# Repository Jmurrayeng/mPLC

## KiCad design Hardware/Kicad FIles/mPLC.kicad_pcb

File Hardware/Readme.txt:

Minimally viable PLC like device based on an RP2040

The board requires a 24VDC power supply and produces a 10V and 5V power supply on the power out connectors
The internal 3.3VDC power supply supply is accessable via the programming/expansion header

There are 11 24VDC inputs (gpio 0 to 10) and 11 open collector outputs (gpio 11-22)
The 4 ADC (gpio 26 to 29) are suitable for 0-10V

The remaining 4 gpio are taken to the programming/expansion header along with serial wire debug

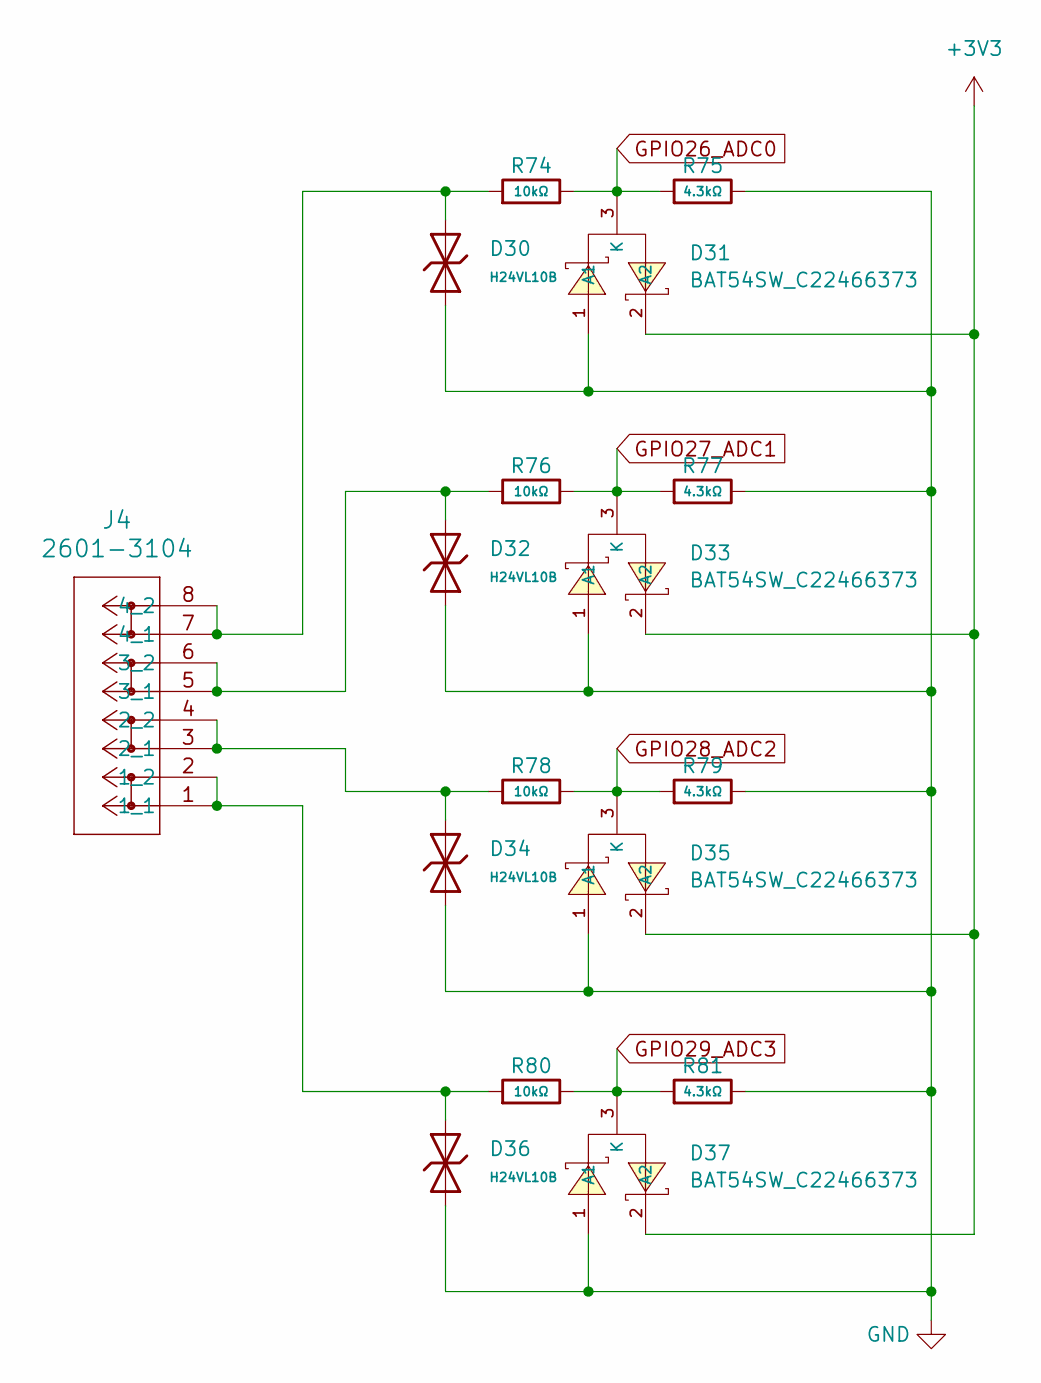
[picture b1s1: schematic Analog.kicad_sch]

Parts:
D30, D32, D34, D36: H24VL10B; D_DFN1006-2L; Part H24VL10B; LCSC C20617912
D31, D33, D35, D37: BAT54SW_C22466373; SOT-323-3_L2.0-W1.3-P1.30-LS2.1-BR-2; Part BAT54SW; LCSC C22466373
J4: 2601-3104; CONN4_2601-3104_WAG
R74, R76, R78, R80: 10kΩ; R_0805; Overload Voltage (Max) 150V; Tolerance ±1%; Part 0805W8F1002T5E; LCSC C17414
R75, R77, R79, R81: 4.3kΩ; R_0805; Overload Voltage (Max) 150V; Tolerance ±1%; Part 0805W8F4301T5E; LCSC C17667

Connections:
+3V3: D31.2 (A2), D33.2 (A2), D35.2 (A2), D37.2 (A2); also elsewhere on the board
GND: D30.1, D31.1 (A1), D32.1, D33.1 (A1), D34.1, D35.1 (A1), D36.1, D37.1 (A1), R75.2, R77.2, R79.2, R81.2; also elsewhere on the board
GPIO26_ADC0: D31.3 (K), R74.2, R75.1; also elsewhere on the board
GPIO27_ADC1: D33.3 (K), R76.2, R77.1; also elsewhere on the board
GPIO28_ADC2: D35.3 (K), R78.2, R79.1; also elsewhere on the board
GPIO29_ADC3: D37.3 (K), R80.2, R81.1; also elsewhere on the board
unnamed: D36.2, J4.1 (1_1), J4.2 (1_2), R80.1
unnamed: D34.2, J4.3 (2_1), J4.4 (2_2), R78.1
unnamed: D32.2, J4.5 (3_1), J4.6 (3_2), R76.1
unnamed: D30.2, J4.7 (4_1), J4.8 (4_2), R74.1

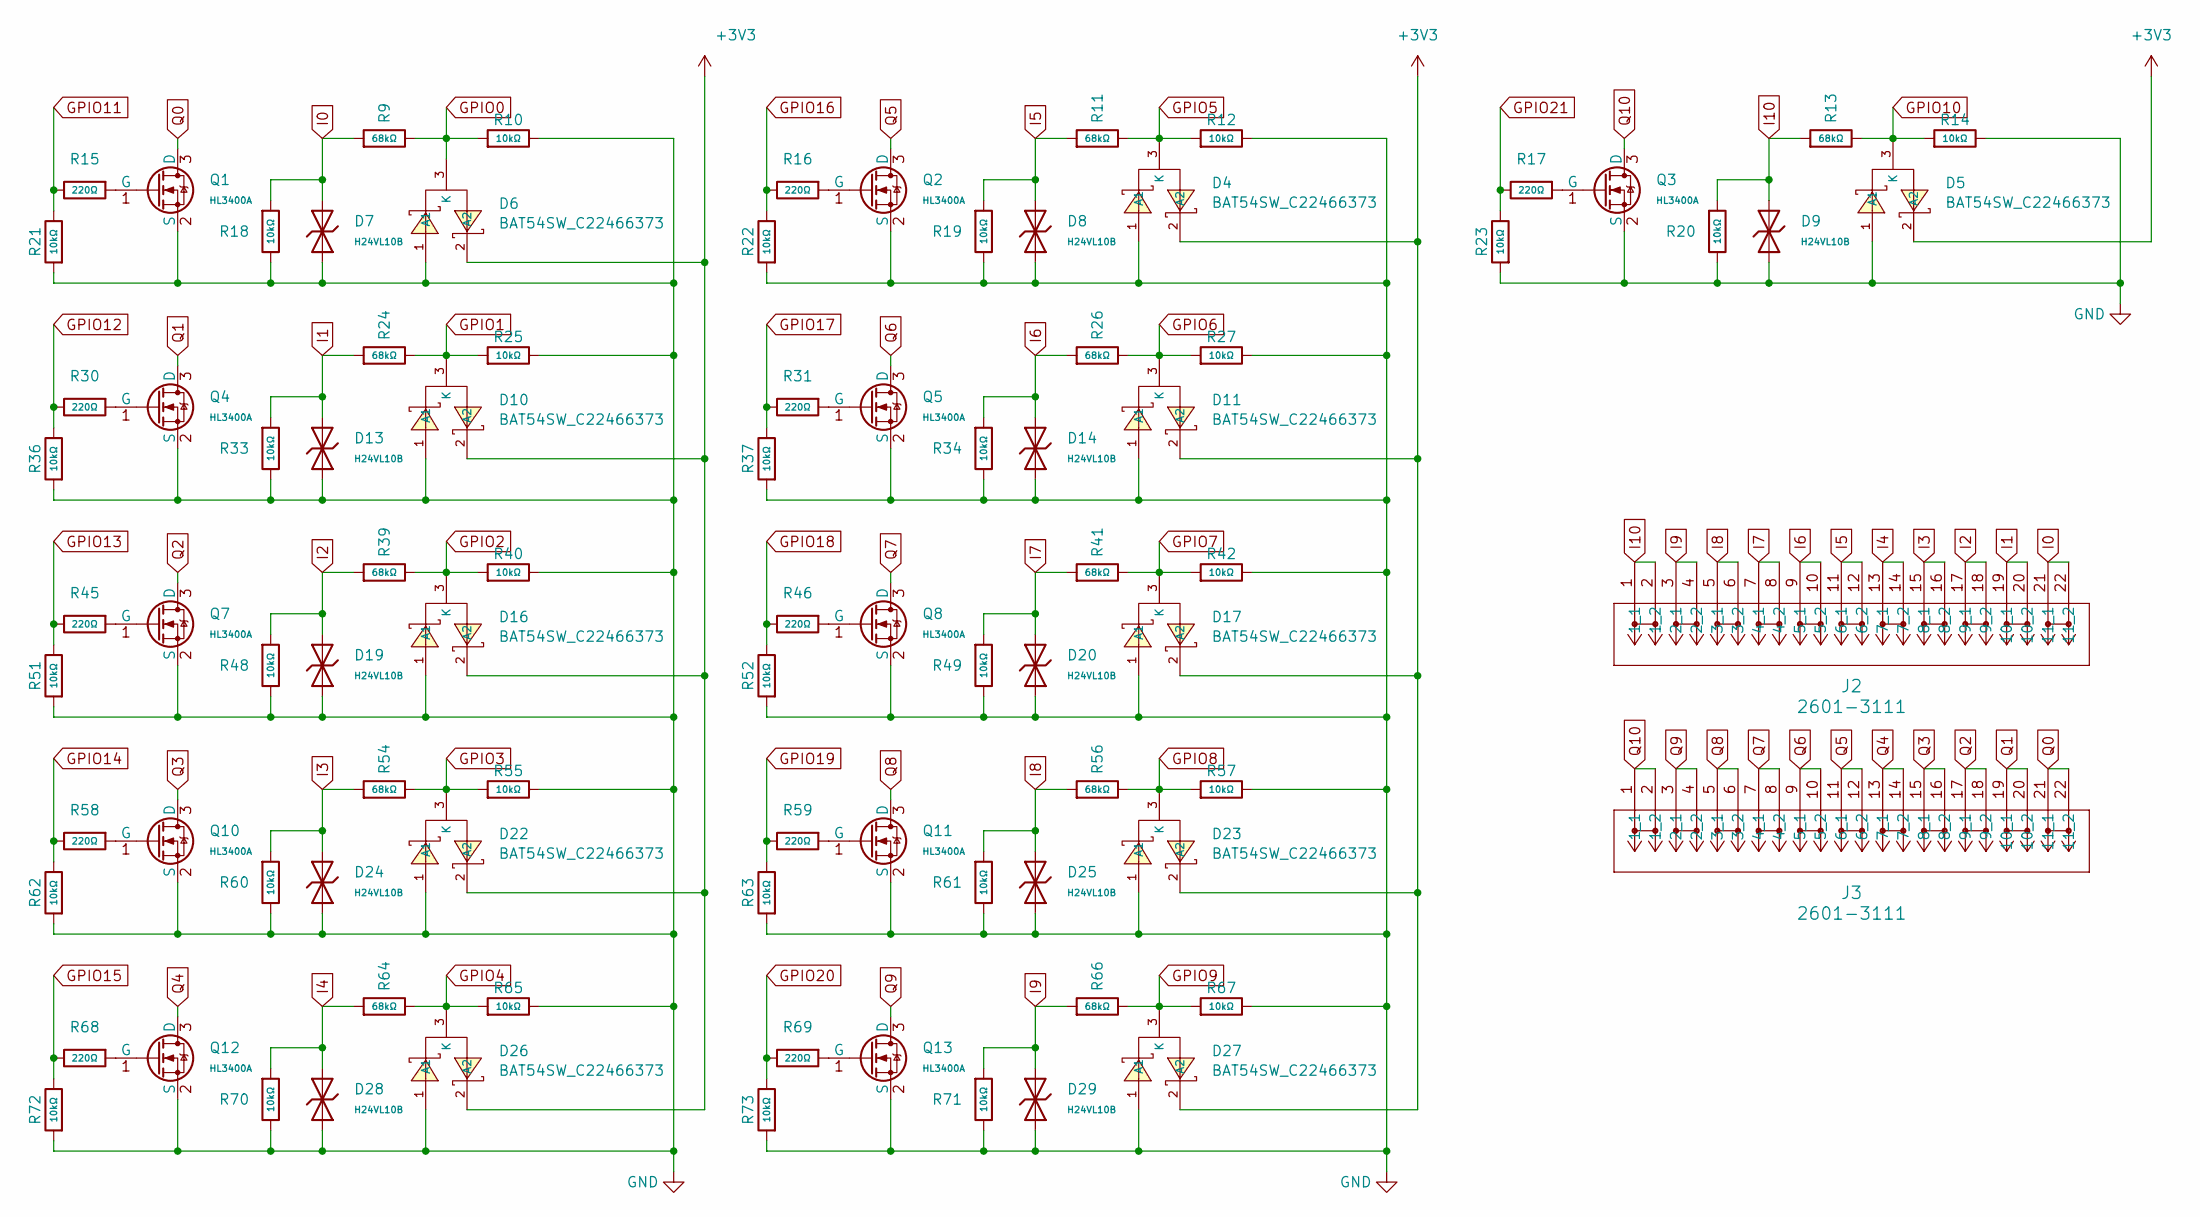
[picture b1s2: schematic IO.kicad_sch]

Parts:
D4, D5, D6, D10, D11, D16, D17, D22, D23, D26, D27: BAT54SW_C22466373; SOT-323-3_L2.0-W1.3-P1.30-LS2.1-BR-2; Part BAT54SW; LCSC C22466373
D7, D8, D9, D13, D14, D19, D20, D24, D25, D28, D29: H24VL10B; D_DFN1006-2L; Part H24VL10B; LCSC C20617912
J2, J3: 2601-3111; CONN11_2601-3111_WAG
Q1, Q2, Q3, Q4, Q5, Q7, Q8, Q10, Q11, Q12, Q13: HL3400A; Q_SOT-23; Part HL3400A; LCSC C7420348
R9, R11, R13, R24, R26, R39, R41, R54, R56, R64, R66: 68kΩ; R_0805; Overload Voltage (Max) 150V; Tolerance ±1%; Part 0805W8F6802T5E; LCSC C17801
R10, R12, R14, R21, R22, R23, R25, R27, R36, R37, R40, R42, R51, R52, R55, R57, R62, R63, R65, R67, R72, R73: 10kΩ; R_0805; Overload Voltage (Max) 150V; Tolerance ±1%; Part 0805W8F1002T5E; LCSC C17414
R15, R16, R17, R30, R31, R45, R46, R58, R59, R68, R69: 220Ω; R_0805; Overload Voltage (Max) 150V; Tolerance ±1%; Part 0805W8F2200T5E; LCSC C17557
R18, R19, R20, R33, R34, R48, R49, R60, R61, R70, R71: 10kΩ; R_1206; Overload Voltage (Max) 200V; Tolerance ±1%; Part 1206W4F1002T5E; LCSC C17902

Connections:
+3V3: D4.2 (A2), D5.2 (A2), D6.2 (A2), D10.2 (A2), D11.2 (A2), D16.2 (A2), D17.2 (A2), D22.2 (A2), D23.2 (A2), D26.2 (A2), D27.2 (A2); also elsewhere on the board
GND: D4.1 (A1), D5.1 (A1), D6.1 (A1), D7.1, D8.1, D9.1, D10.1 (A1), D11.1 (A1), D13.1, D14.1, D16.1 (A1), D17.1 (A1), D19.1, D20.1, D22.1 (A1), D23.1 (A1), D24.1, D25.1, D26.1 (A1), D27.1 (A1), D28.1, D29.1, Q1.2 (S), Q2.2 (S), Q3.2 (S), Q4.2 (S), Q5.2 (S), Q7.2 (S), Q8.2 (S), Q10.2 (S), Q11.2 (S), Q12.2 (S), Q13.2 (S), R10.2, R12.2, R14.2, R18.2, R19.2, R20.2, R21.1, R22.1, R23.1, R25.2, R27.2, R33.2, R34.2, R36.1, R37.1, R40.2, R42.2, R48.2, R49.2, R51.1, R52.1, R55.2, R57.2, R60.2, R61.2, R62.1, R63.1, R65.2, R67.2, R70.2, R71.2, R72.1, R73.1; also elsewhere on the board
GPIO0: D6.3 (K), R9.2, R10.1; also elsewhere on the board
GPIO1: D10.3 (K), R24.2, R25.1; also elsewhere on the board
GPIO2: D16.3 (K), R39.2, R40.1; also elsewhere on the board
GPIO3: D22.3 (K), R54.2, R55.1; also elsewhere on the board
GPIO4: D26.3 (K), R64.2, R65.1; also elsewhere on the board
GPIO5: D4.3 (K), R11.2, R12.1; also elsewhere on the board
GPIO6: D11.3 (K), R26.2, R27.1; also elsewhere on the board
GPIO7: D17.3 (K), R41.2, R42.1; also elsewhere on the board
GPIO8: D23.3 (K), R56.2, R57.1; also elsewhere on the board
GPIO9: D27.3 (K), R66.2, R67.1; also elsewhere on the board
GPIO10: D5.3 (K), R13.2, R14.1; also elsewhere on the board
GPIO11: R15.2, R21.2; also elsewhere on the board
GPIO12: R30.2, R36.2; also elsewhere on the board
GPIO13: R45.2, R51.2; also elsewhere on the board
GPIO14: R58.2, R62.2; also elsewhere on the board
GPIO15: R68.2, R72.2; also elsewhere on the board
GPIO16: R16.2, R22.2; also elsewhere on the board
GPIO17: R31.2, R37.2; also elsewhere on the board
GPIO18: R46.2, R52.2; also elsewhere on the board
GPIO19: R59.2, R63.2; also elsewhere on the board
GPIO20: R69.2, R73.2; also elsewhere on the board
GPIO21: R17.2, R23.2; also elsewhere on the board
I0: D7.2, J2.21 (11_1), J2.22 (11_2), R9.1, R18.1
I1: D13.2, J2.19 (10_1), J2.20 (10_2), R24.1, R33.1
I2: D19.2, J2.17 (9_1), J2.18 (9_2), R39.1, R48.1
I3: D24.2, J2.15 (8_1), J2.16 (8_2), R54.1, R60.1
I4: D28.2, J2.13 (7_1), J2.14 (7_2), R64.1, R70.1
I5: D8.2, J2.11 (6_1), J2.12 (6_2), R11.1, R19.1
I6: D14.2, J2.9 (5_1), J2.10 (5_2), R26.1, R34.1
I7: D20.2, J2.7 (4_1), J2.8 (4_2), R41.1, R49.1
I8: D25.2, J2.5 (3_1), J2.6 (3_2), R56.1, R61.1
I9: D29.2, J2.3 (2_1), J2.4 (2_2), R66.1, R71.1
I10: D9.2, J2.1 (1_1), J2.2 (1_2), R13.1, R20.1
unnamed: Q1.1 (G), R15.1
unnamed: Q2.1 (G), R16.1
unnamed: Q3.1 (G), R17.1
unnamed: Q4.1 (G), R30.1
unnamed: Q5.1 (G), R31.1
unnamed: Q7.1 (G), R45.1
unnamed: Q8.1 (G), R46.1
unnamed: Q10.1 (G), R58.1
unnamed: Q11.1 (G), R59.1
unnamed: Q12.1 (G), R68.1
unnamed: Q13.1 (G), R69.1
Q0: J3.21 (11_1), J3.22 (11_2), Q1.3 (D)
Q1: J3.19 (10_1), J3.20 (10_2), Q4.3 (D)
Q2: J3.17 (9_1), J3.18 (9_2), Q7.3 (D)
Q3: J3.15 (8_1), J3.16 (8_2), Q10.3 (D)
Q4: J3.13 (7_1), J3.14 (7_2), Q12.3 (D)
Q5: J3.11 (6_1), J3.12 (6_2), Q2.3 (D)
Q6: J3.9 (5_1), J3.10 (5_2), Q5.3 (D)
Q7: J3.7 (4_1), J3.8 (4_2), Q8.3 (D)
Q8: J3.5 (3_1), J3.6 (3_2), Q11.3 (D)
Q9: J3.3 (2_1), J3.4 (2_2), Q13.3 (D)
Q10: J3.1 (1_1), J3.2 (1_2), Q3.3 (D)

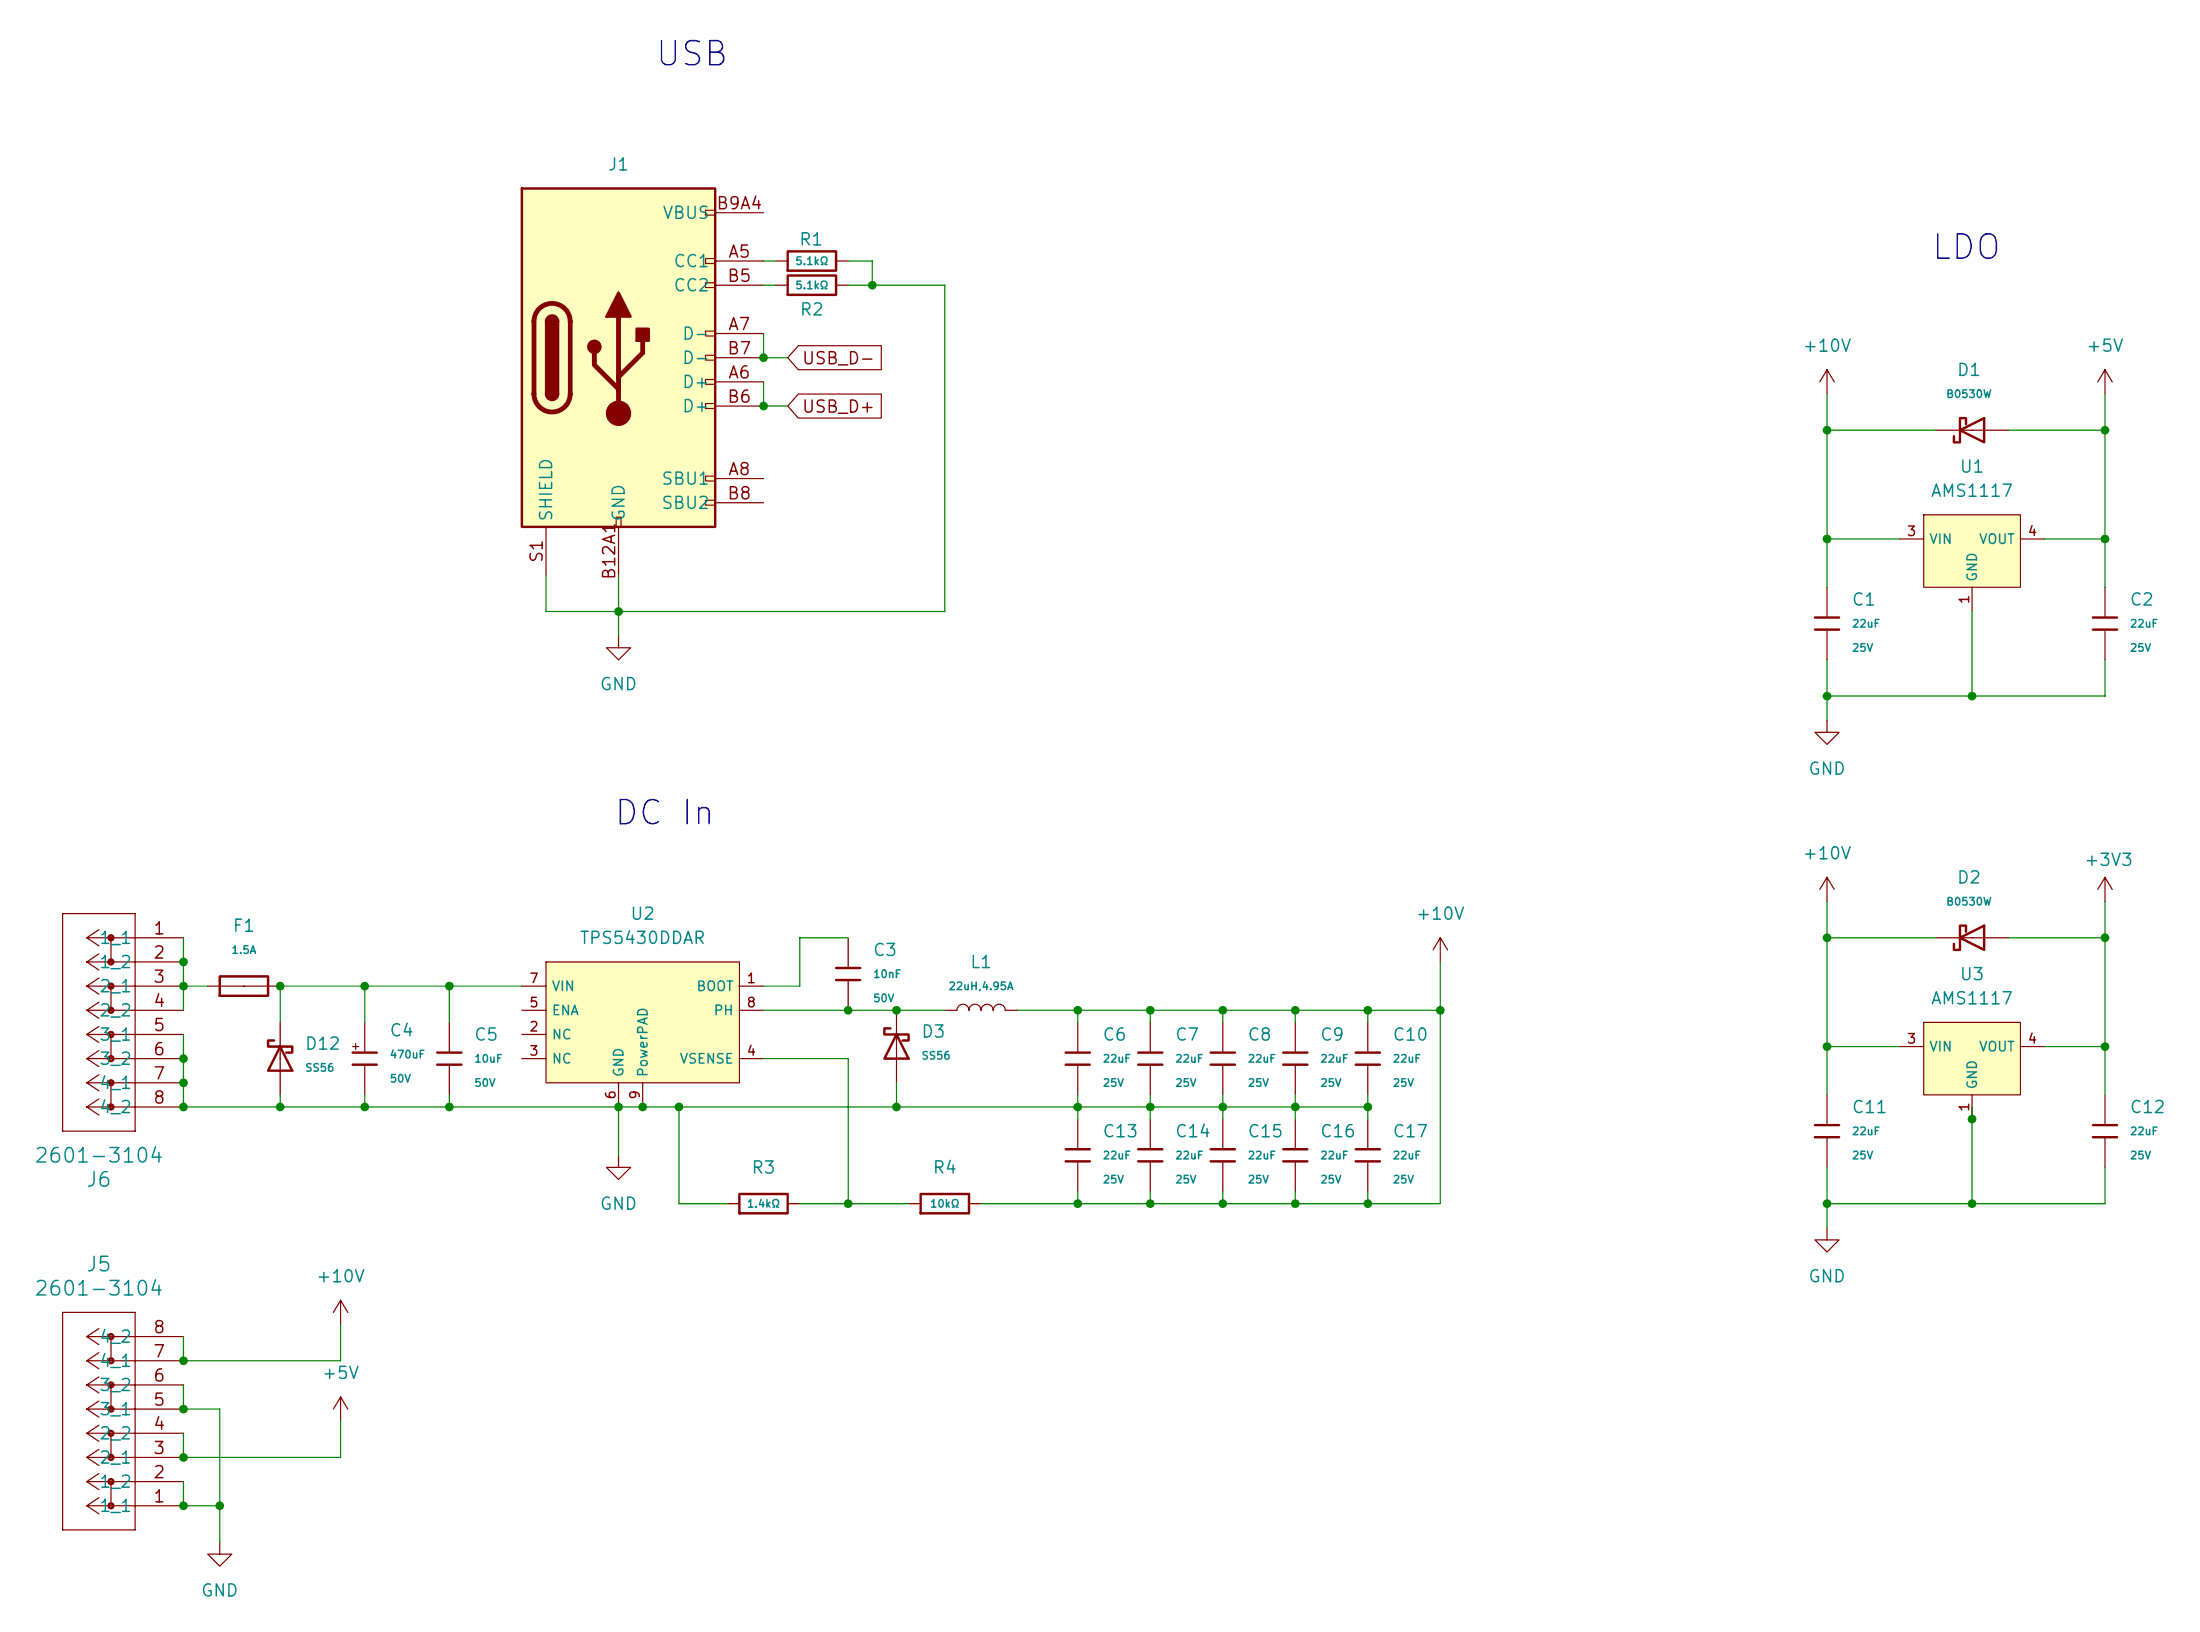
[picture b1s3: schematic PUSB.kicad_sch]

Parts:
C1, C2, C11, C12: 22uF; C_0805; Voltage Rated 25V; Tolerance ±20%; Part CL21A226MAQNNNE; LCSC C45783
C3: 10nF; C_0805; Voltage Rated 50V; Tolerance ±10%; Part CL21B103KBANNNC; LCSC C1710
C4: 470uF; C_Plugin,D10xL16mm; Voltage Rated 50V; Part EGT477M1HG16RRS0P; LCSC C3015599
C5: 10uF; C_0805; Voltage Rated 50V; Tolerance ±10%; Part GRM21BR61H106KE43L; LCSC C440198
C6, C7, C8, C9, C10, C13, C14, C15, C16, C17: 22uF; C_1206; Voltage Rated 25V; Tolerance ±10%; Part CL31A226KAHNNNE; LCSC C12891
D1, D2: B0530W; D_SOD-123; Part B0530W; LCSC C7502708
D3, D12: SS56; D_SMC; Part SS56; LCSC C2898934
F1: 1.5A; F_1206; Part SRF1206P150; LCSC C2838983
J1: Connector, USB-TYPE-C-16P; TYPE-C-SMD_HX-TYPE-C-16PIN; LCSC C2927039
J5, J6: 2601-3104; CONN4_2601-3104_WAG
L1: 22uH,4.95A; L_SMD,12.5x12.5mm; Part SMDRI129-220MT; LCSC C2924827
R1, R2: 5.1kΩ; R_0805; Overload Voltage (Max) 150V; Tolerance ±1%; Part 0805W8F5101T5E; LCSC C27834
R3: 1.4kΩ; R_0805; Part CR0805F81401G; LCSC C101470
R4: 10kΩ; R_0805; Overload Voltage (Max) 150V; Tolerance ±1%; Part 0805W8F1002T5E; LCSC C17414
U1: AMS1117; SOT-223_L6.5-W3.5-P2.30-LS7.0-BR; Output Voltage 5V~5V; Dropout Voltage 1.3V@(1A); Part AMS1117-5.0; LCSC C6187
U2: TPS5430DDAR; ESOP-8_L4.9-W3.9-P1.27-LS6.0-TL-EP; Output Voltage 1.221V~32.04V; Input Voltage 5.5V~36V; Part TPS5430DDAR; LCSC C9864
U3: AMS1117; SOT-223-3_L6.5-W3.4-P2.30-LS7.0-BR; Output Voltage 3.3V~3.3V; Dropout Voltage 1.3V@(800mA); Part AMS1117-3.3; LCSC C6186

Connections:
+3V3: C12.1, D2.2, U3.2 (VOUT), U3.4 (VOUT); also elsewhere on the board
+5V: C2.1, D1.2, J5.3 (2_1), J5.4 (2_2), U1.2 (VOUT), U1.4 (VOUT)
+10V: C1.1, C6.1, C7.1, C8.1, C9.1, C10.1, C11.1, C13.2, C14.2, C15.2, C16.2, C17.2, D1.1, D2.1, J5.7 (4_1), J5.8 (4_2), L1.2, R4.2, U1.3 (VIN), U3.3 (VIN)
GND: C1.2, C2.2, C4.2, C5.2, C6.2, C7.2, C8.2, C9.2, C10.2, C11.2, C12.2, C13.1, C14.1, C15.1, C16.1, C17.1, D3.2, D12.2, J1.A12B1 (GND), J1.B12A1 (GND), J1.S1 (SHIELD), J5.1 (1_1), J5.2 (1_2), J5.5 (3_1), J5.6 (3_2), J6.5 (3_1), J6.6 (3_2), J6.7 (4_1), J6.8 (4_2), R1.2, R2.2, R3.1, U1.1 (GND), U2.6 (GND), U2.9 (PowerPAD), U3.1 (GND); also elsewhere on the board
unnamed: J1.A5 (CC1), R1.1
unnamed: J1.B5 (CC2), R2.1
unnamed: J1.A9B4 (VBUS), J1.B9A4 (VBUS)
unnamed: F1.1, J6.1 (1_1), J6.2 (1_2), J6.3 (2_1), J6.4 (2_2)
unnamed: C3.1, U2.1 (BOOT)
unnamed: C3.2, D3.1, L1.1, U2.8 (PH)
unnamed: C4.1, C5.1, D12.1, F1.2, U2.7 (VIN)
unnamed: R3.2, R4.1, U2.4 (VSENSE)
USB_D+: J1.A6 (D+), J1.B6 (D+); also elsewhere on the board
USB_D-: J1.A7 (D-), J1.B7 (D-); also elsewhere on the board

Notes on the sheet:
LDO
USB
DC In

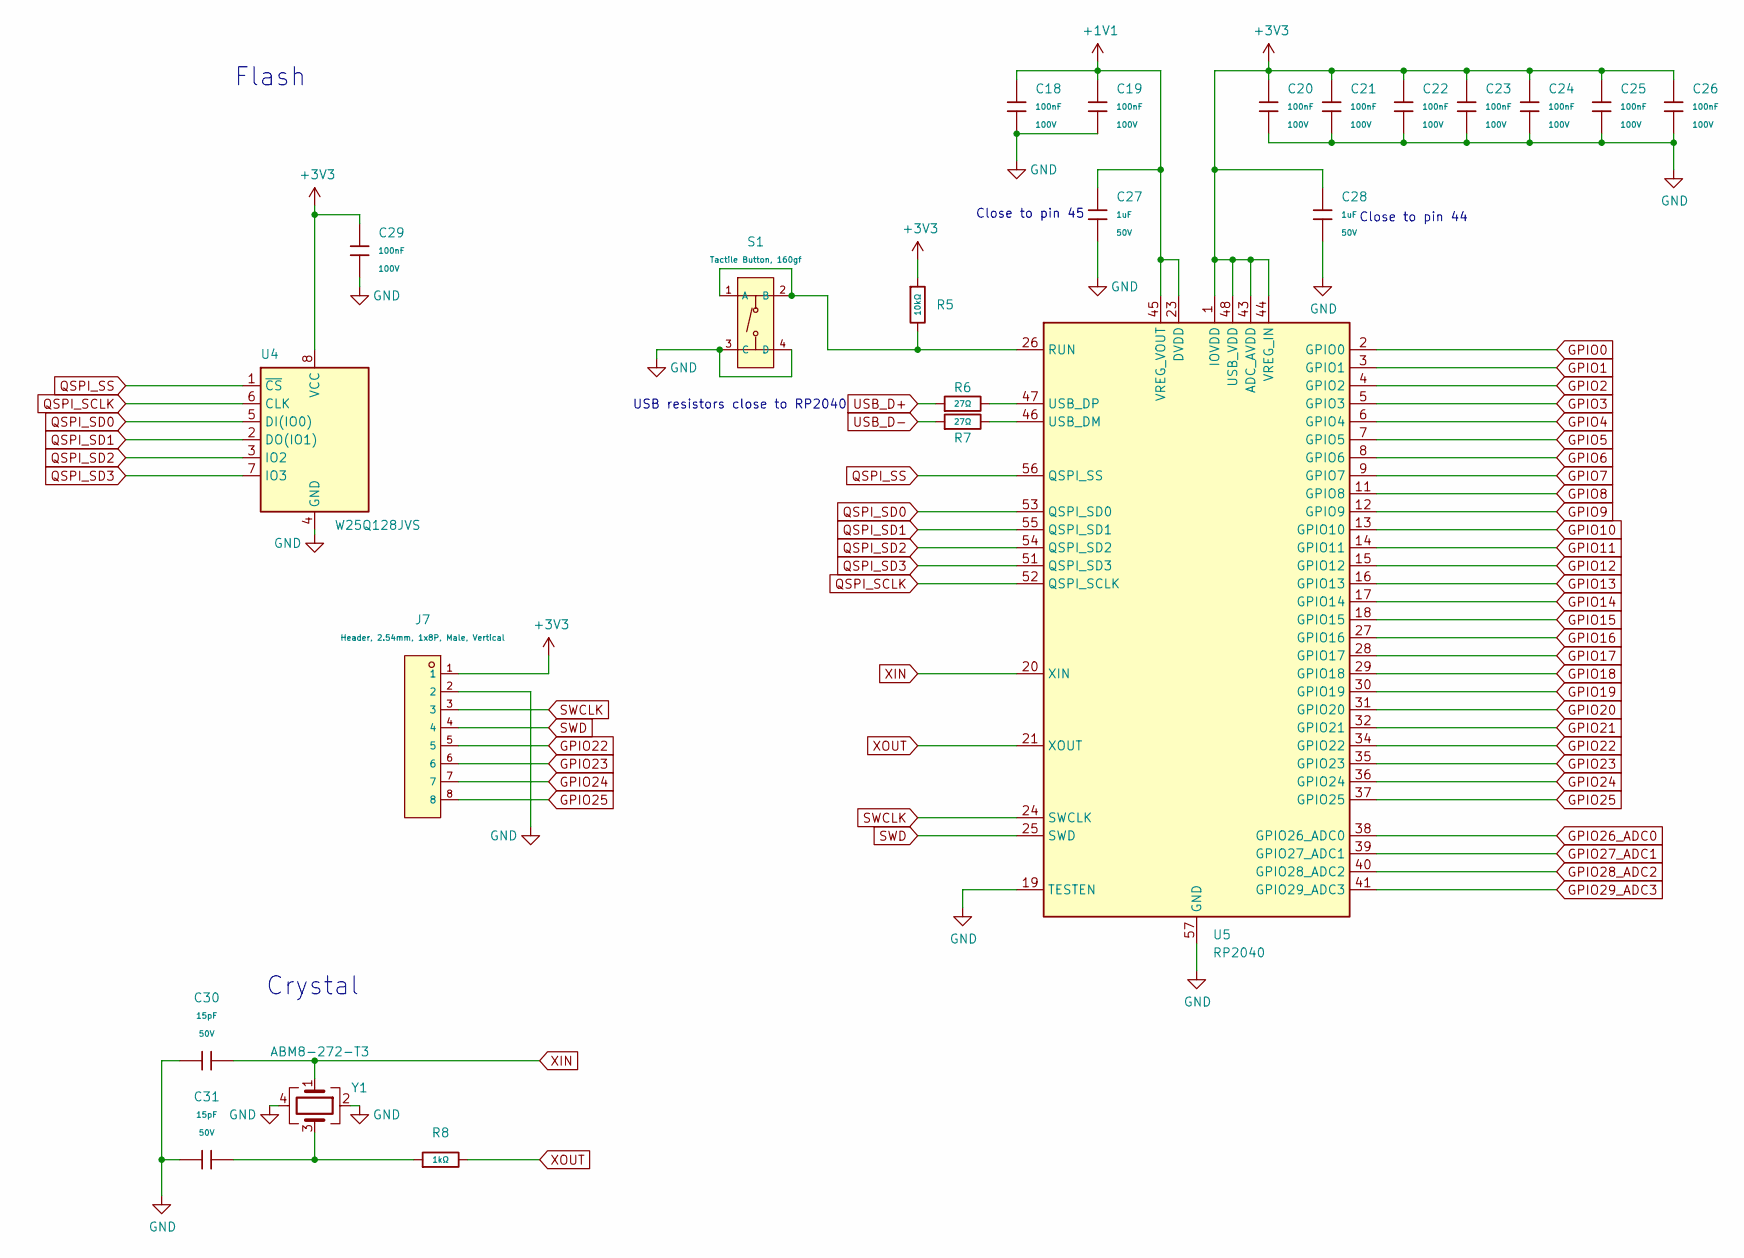
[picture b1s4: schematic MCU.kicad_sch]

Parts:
C18, C19, C20, C21, C22, C23, C24, C25, C26, C29: 100nF; C_0805; Voltage Rated 100V; Tolerance ±10%; Part CL21B104KCFNNNE; LCSC C28233
C27, C28: 1uF; C_0805; Voltage Rated 50V; Tolerance ±10%; Part CL21B105KBFNNNE; LCSC C28323
C30, C31: 15pF; C_0805; Voltage Rated 50V; Tolerance ±5%; Part CC0805JRNPO9BN150; LCSC C107110
J7: Header, 2.54mm, 1x8P, Male, Vertical; HDR-TH_8P-P2.54-V-M; Part PH-00250; LCSC C2829996
R5: 10kΩ; R_0805; Overload Voltage (Max) 150V; Tolerance ±1%; Part 0805W8F1002T5E; LCSC C17414
R6, R7: 27Ω; R_0805; Overload Voltage (Max) 150V; Tolerance ±1%; Part 0805W8F270JT5E; LCSC C17594
R8: 1kΩ; R_0805; Overload Voltage (Max) 150V; Tolerance ±1%; Part 0805W8F1001T5E; LCSC C17513
S1: Tactile Button, 160gf; SW-SMD_4P-L5.1-W5.1-P3.70-LS6.5-TL-2; Voltage Rating (Dc) 12V; Part TS-1187A-B-A-B; LCSC C318884
U4: W25Q128JVS; SOIC-8_5.23x5.23mm_P1.27mm
U5: RP2040; QFN-56-1EP_7x7mm_P0.4mm_EP3.2x3.2mm
Y1: ABM8-272-T3; Crystal_SMD_3225-4Pin_3.2x2.5mm

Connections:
+1V1: C18.1, C19.1, C27.1, U5.23 (DVDD), U5.45 (VREG_VOUT), U5.50 (DVDD)
+3V3: C20.1, C21.1, C22.1, C23.1, C24.1, C25.1, C26.1, C28.1, C29.1, J7.1, R5.1, U4.8 (VCC), U5.1 (IOVDD), U5.10 (IOVDD), U5.22 (IOVDD), U5.33 (IOVDD), U5.42 (IOVDD), U5.43 (ADC_AVDD), U5.44 (VREG_IN), U5.48 (USB_VDD), U5.49 (IOVDD); also elsewhere on the board
GND: C18.2, C19.2, C20.2, C21.2, C22.2, C23.2, C24.2, C25.2, C26.2, C27.2, C28.2, C29.2, C30.1, C31.1, J7.2, S1.3 (C), S1.4 (D), U4.4 (GND), U5.19 (TESTEN), U5.57 (GND), Y1.2, Y1.4; also elsewhere on the board
GPIO0: U5.2 (GPIO0); also elsewhere on the board
GPIO1: U5.3 (GPIO1); also elsewhere on the board
GPIO2: U5.4 (GPIO2); also elsewhere on the board
GPIO3: U5.5 (GPIO3); also elsewhere on the board
GPIO4: U5.6 (GPIO4); also elsewhere on the board
GPIO5: U5.7 (GPIO5); also elsewhere on the board
GPIO6: U5.8 (GPIO6); also elsewhere on the board
GPIO7: U5.9 (GPIO7); also elsewhere on the board
GPIO8: U5.11 (GPIO8); also elsewhere on the board
GPIO9: U5.12 (GPIO9); also elsewhere on the board
GPIO10: U5.13 (GPIO10); also elsewhere on the board
GPIO11: U5.14 (GPIO11); also elsewhere on the board
GPIO12: U5.15 (GPIO12); also elsewhere on the board
GPIO13: U5.16 (GPIO13); also elsewhere on the board
GPIO14: U5.17 (GPIO14); also elsewhere on the board
GPIO15: U5.18 (GPIO15); also elsewhere on the board
GPIO16: U5.27 (GPIO16); also elsewhere on the board
GPIO17: U5.28 (GPIO17); also elsewhere on the board
GPIO18: U5.29 (GPIO18); also elsewhere on the board
GPIO19: U5.30 (GPIO19); also elsewhere on the board
GPIO20: U5.31 (GPIO20); also elsewhere on the board
GPIO21: U5.32 (GPIO21); also elsewhere on the board
GPIO22: J7.5, U5.34 (GPIO22)
GPIO23: J7.6, U5.35 (GPIO23)
GPIO24: J7.7, U5.36 (GPIO24)
GPIO25: J7.8, U5.37 (GPIO25)
GPIO26_ADC0: U5.38 (GPIO26_ADC0); also elsewhere on the board
GPIO27_ADC1: U5.39 (GPIO27_ADC1); also elsewhere on the board
GPIO28_ADC2: U5.40 (GPIO28_ADC2); also elsewhere on the board
GPIO29_ADC3: U5.41 (GPIO29_ADC3); also elsewhere on the board
unnamed: C31.2, R8.1, Y1.3
unnamed: R5.2, S1.1 (A), S1.2 (B), U5.26 (RUN)
unnamed: R7.2, U5.46 (USB_DM)
unnamed: R6.2, U5.47 (USB_DP)
QSPI_SCLK: U4.6 (CLK), U5.52 (QSPI_SCLK)
QSPI_SD0: U4.5 (DI(IO0)), U5.53 (QSPI_SD0)
QSPI_SD1: U4.2 (DO(IO1)), U5.55 (QSPI_SD1)
QSPI_SD2: U4.3 (IO2), U5.54 (QSPI_SD2)
QSPI_SD3: U4.7 (IO3), U5.51 (QSPI_SD3)
QSPI_SS: U4.1 (~CS), U5.56 (QSPI_SS)
SWCLK: J7.3, U5.24 (SWCLK)
SWD: J7.4, U5.25 (SWD)
USB_D+: R6.1; also elsewhere on the board
USB_D-: R7.1; also elsewhere on the board
XIN: C30.2, U5.20 (XIN), Y1.1
XOUT: R8.2, U5.21 (XOUT)

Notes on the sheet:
USB resistors close to RP2040
Close to pin 44
Crystal
Flash
Close to pin 45

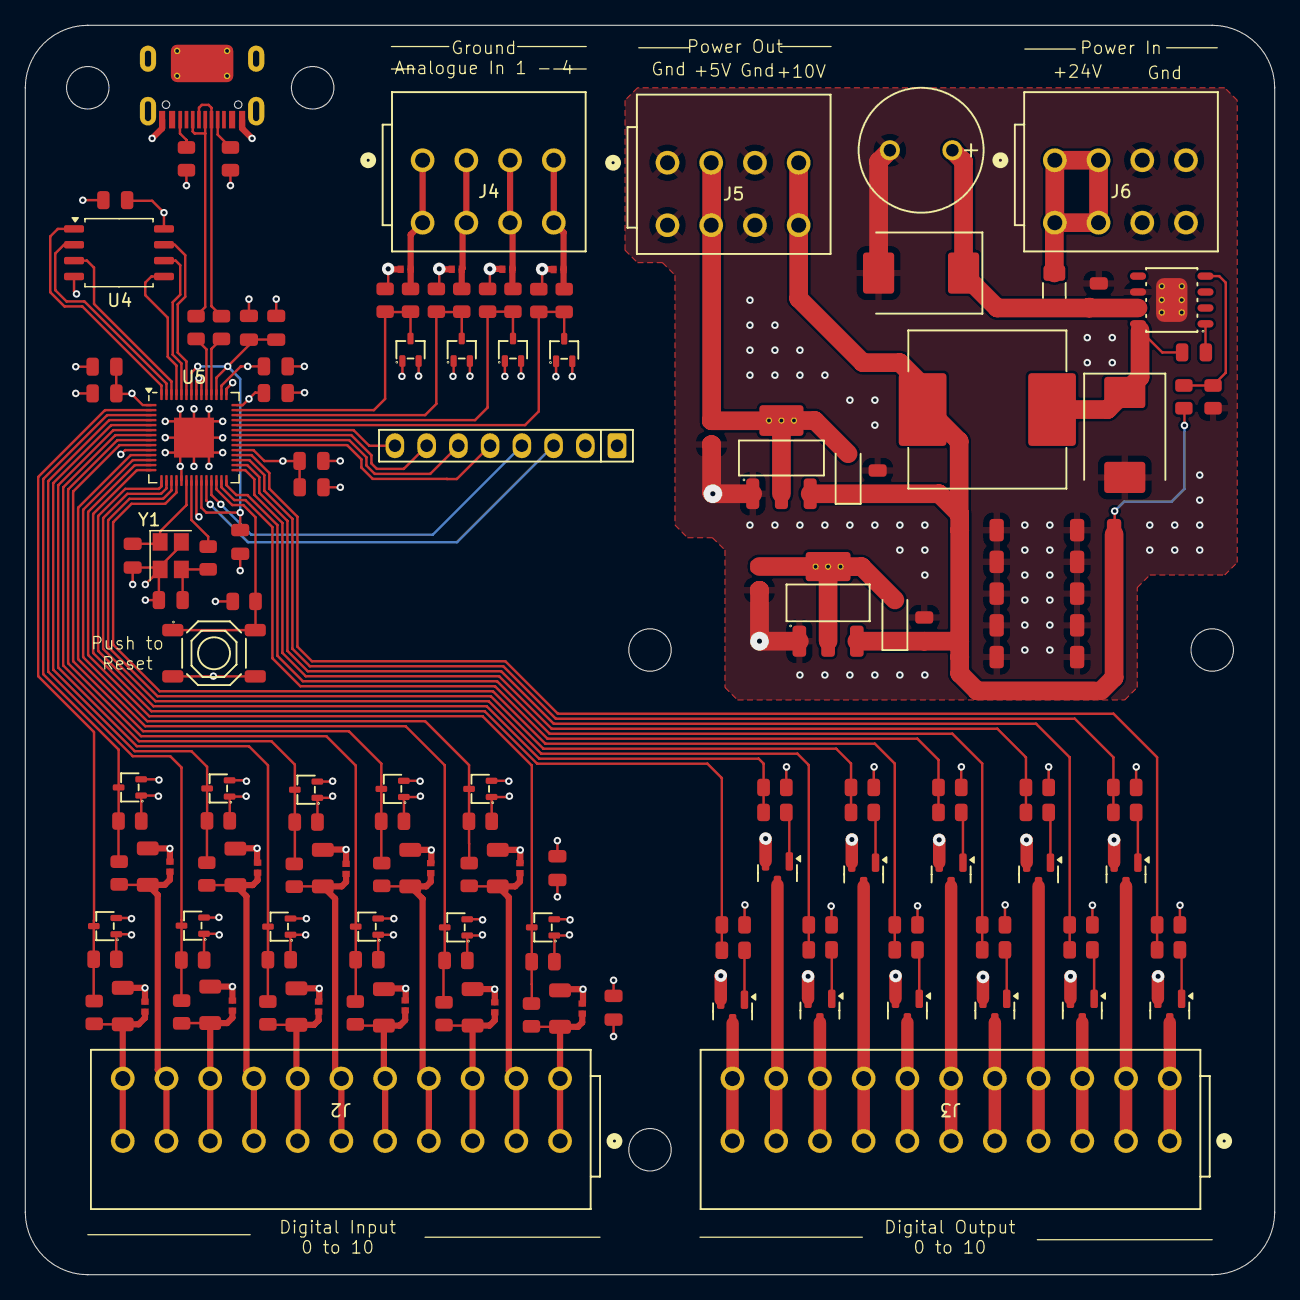
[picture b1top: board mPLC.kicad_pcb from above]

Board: 4 copper layers, 100.0 x 100.0 mm, 163 parts (0 on the bottom side), 96 nets.

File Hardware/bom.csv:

Designator,Footprint,Quantity,Value,LCSC Part #
"C1, C11, C12, C2",C_0805,4,22uF,C45783
"C10, C13, C14, C15, C16, C17, C6, C7, C8, C9",C_1206,10,22uF,C12891
"C18, C19, C20, C21, C22, C23, C24, C25, C26, C29",C_0805,10,100nF,C28233
"C27, C28",C_0805,2,1uF,C28323
C3,C_0805,1,10nF,C1710
"C30, C31",C_0805,2,15pF,C107110
C4,"C_Plugin,D10xL16mm",1,470uF,C3015599
C5,C_0805,1,10uF,C440198
"D1, D2",D_SOD-123,2,B0530W,C7502708
"D10, D11, D16, D17, D22, D23, D26, D27, D31, D33, D35, D37, D4, D5, D6",SOT-323-3_L2.0-W1.3-P1.30-LS2.1-BR-2,15,BAT54SW_C22466373,C22466373
"D13, D14, D19, D20, D24, D25, D28, D29, D30, D32, D34, D36, D7, D8, D9",D_DFN1006-2L,15,H24VL10B,C20617912
D3,D_SMC,1,SS56,C2898934
J1,TYPE-C-SMD_HX-TYPE-C-16PIN,1,"Connector, USB-TYPE-C-16P",C2927039
"J2, J3",CONN11_2601-3111_WAG,2,2601-3111,
"J4, J5, J6",CONN4_2601-3104_WAG,3,2601-3104,
J7,HDR-TH_8P-P2.54-V-M,1,"Header, 2.54mm, 1x8P, Male, Vertical",C2829996
L1,"L_SMD,12.5x12.5mm",1,"22uH,4.95A",C2924827
"Q1, Q10, Q11, Q12, Q13, Q2, Q3, Q4, Q5, Q7, Q8",Q_SOT-23,11,HL3400A,C7420348
"R1, R2",R_0805,2,5.1kΩ,C27834
"R10, R12, R14, R21, R22, R23, R25, R27, R36, R37, R4, R40, R42, R5, R51, R52, R55, R57, R62, R63, R65, R67, R72, R73, R74, R76, R78, R80",R_0805,28,10kΩ,C17414
"R11, R13, R24, R26, R39, R41, R54, R56, R64, R66, R9",R_0805,11,68kΩ,C17801
"R15, R16, R17, R30, R31, R45, R46, R58, R59, R68, R69",R_0805,11,220Ω,C17557
"R18, R19, R20, R33, R34, R48, R49, R60, R61, R70, R71",R_1206,11,10kΩ,C17902
R3,R_0805,1,1.4kΩ,C101470
"R6, R7",R_0805,2,27Ω,C17594
"R75, R77, R79, R81",R_0805,4,4.3kΩ,C17667
R8,R_0805,1,1kΩ,C17513
S1,SW-SMD_4P-L5.1-W5.1-P3.70-LS6.5-TL-2,1,"Tactile Button, 160gf",C318884
U1,SOT-223_L6.5-W3.5-P2.30-LS7.0-BR,1,AMS1117,C6187
U2,ESOP-8_L4.9-W3.9-P1.27-LS6.0-TL-EP,1,TPS5430DDAR,C9864
U3,SOT-223-3_L6.5-W3.4-P2.30-LS7.0-BR,1,AMS1117,C6186
U4,SOIC-8_5.23x5.23mm_P1.27mm,1,W25Q128JVS,
U5,QFN-56-1EP_7x7mm_P0.4mm_EP3.2x3.2mm,1,RP2040,
Y1,Crystal_SMD_3225-4Pin_3.2x2.5mm,1,ABM8-272-T3,

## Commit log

2024-12-14 Create main
2024-12-20 Create main pnuz
2024-12-20 Update main pnuz
2024-12-21 Create main pnuz v2
2024-12-21 Update main pnuz v2
2024-12-22 Update main
2025-01-05 Update main
    G1 command fixed, G2/3 command work in progress
